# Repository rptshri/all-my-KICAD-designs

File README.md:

View this project on [CADLAB.io](https://cadlab.io/project/2196). 

# all-my-KICAD-designs

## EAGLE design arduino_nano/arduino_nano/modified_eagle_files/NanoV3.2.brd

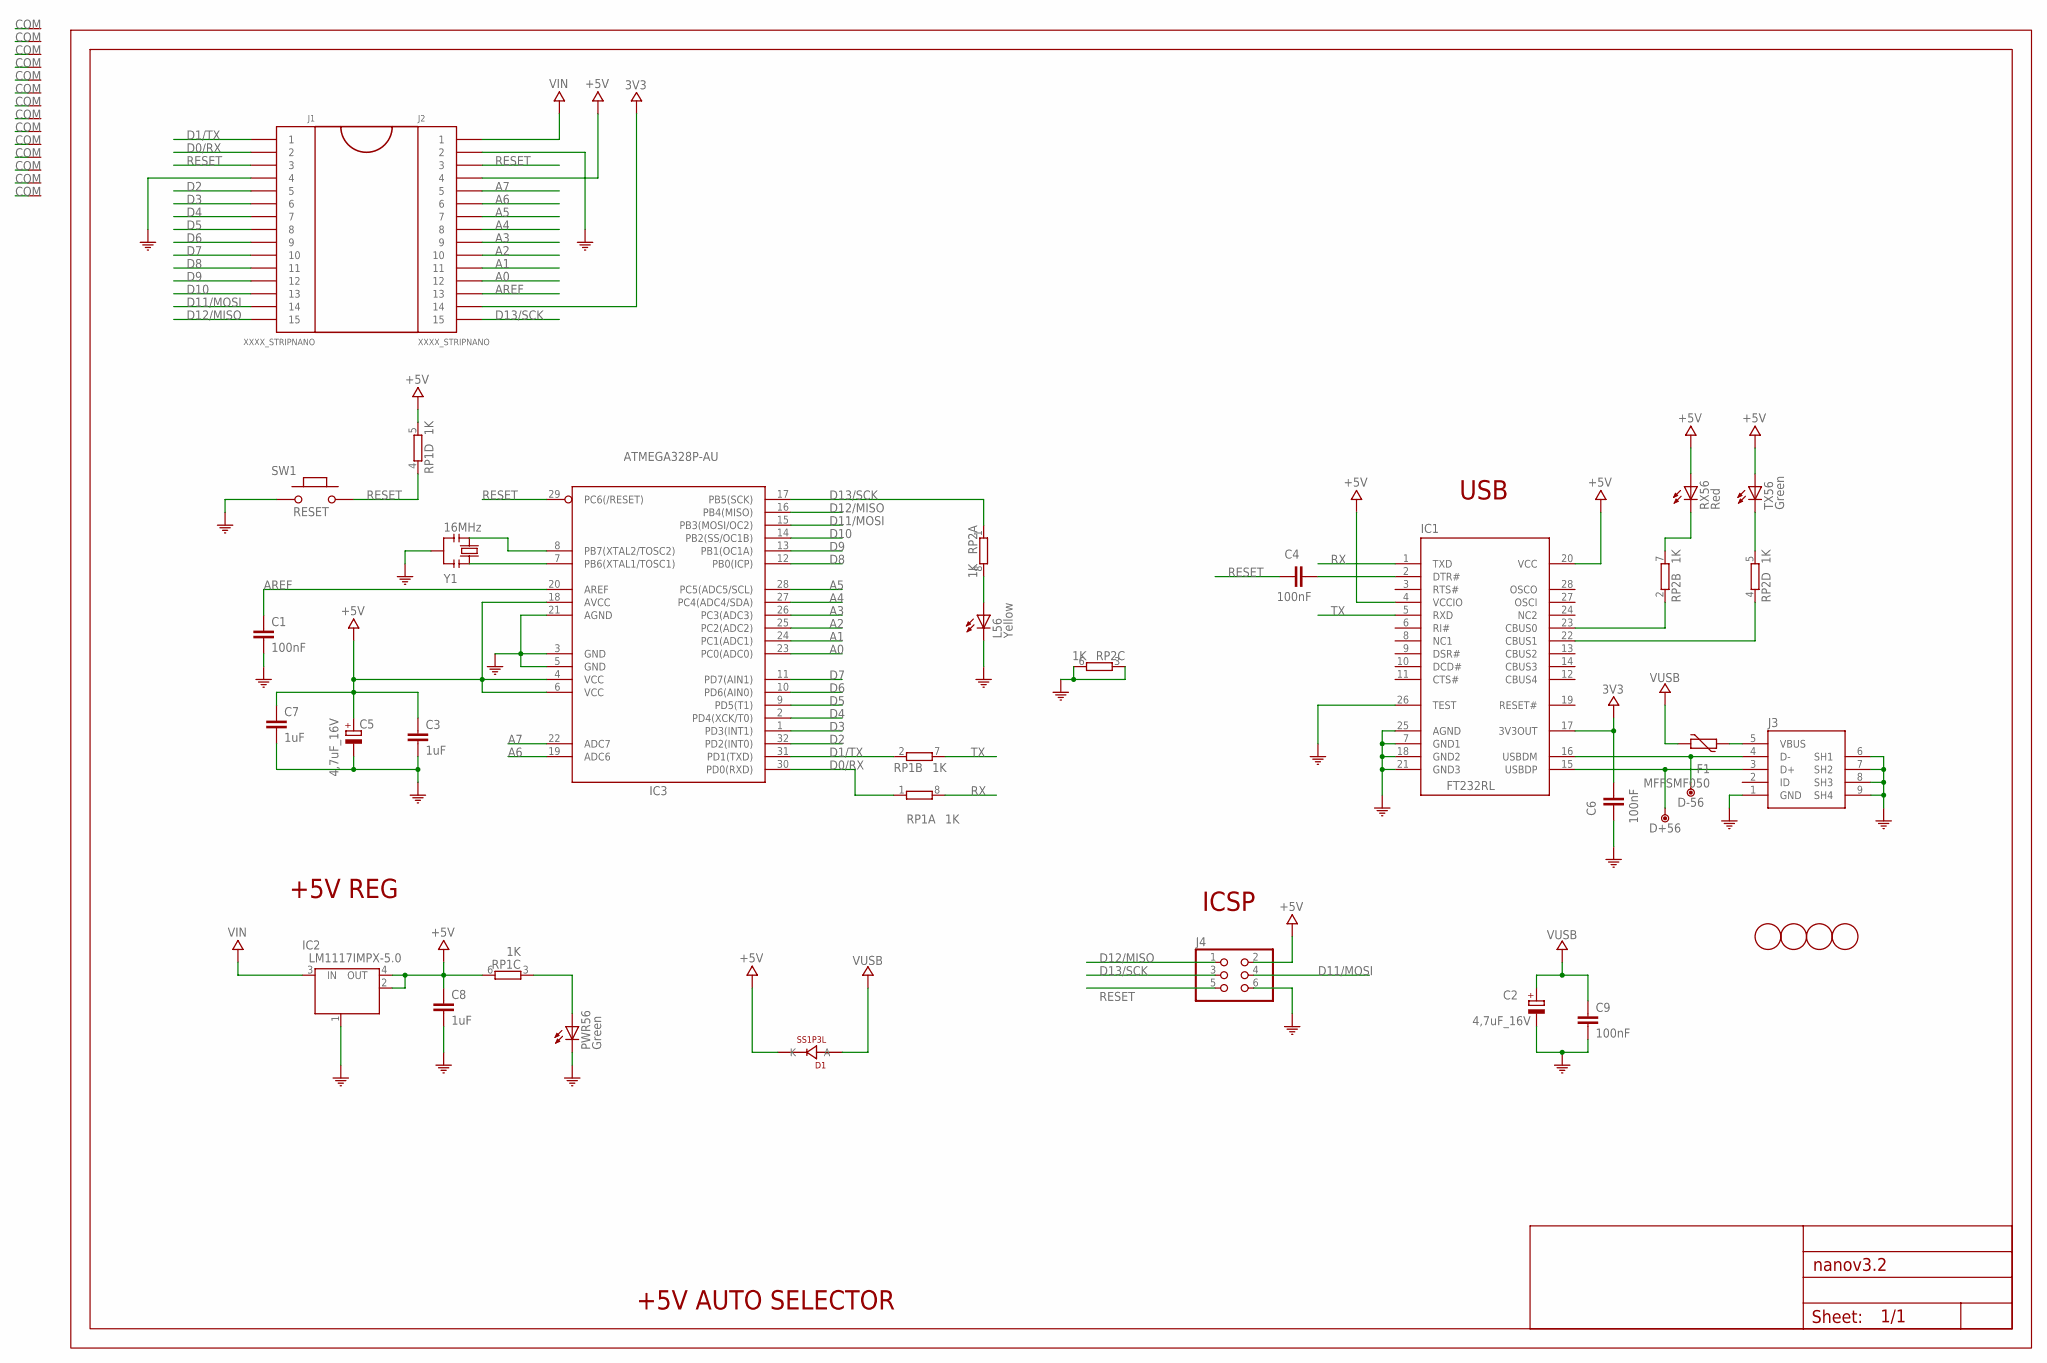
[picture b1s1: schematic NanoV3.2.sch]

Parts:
C1, C4, C6, C9: 100nF; C0603-ROUND
C2, C5: 4,7uF_16V; TAN-A
C3, C7, C8: 1uF; C0603-ROUND
D1: SS1P3L; DO220AAL
D+56: DNP; TP-1.00MM
D-56: DNP; TP-1.00MM
F1: MFFSMF050; 0603-1608X90N
FRAME1: DNP; FRAME
IC1: FT232RL; SSOP28
IC2: LM1117IMPX-5.0; LINEAR_SOT223
IC3: ATMEGA328P-AU; TQFP32-08
J1, J2: XXXX_STRIPNANO; HEAD15-NOSS
J3: 0219_14850; USB-MINI-B_2
J4: 0114_PH254-203DF118A00V; 2X03
L56: Yellow; CHIPLED_0805
PWR56: Green; CHIPLED_0805
RP1, RP2: 1K; CAY16
RX56: Red; CHIPLED_0805
SW1: RESET; SMD_157SW
TX56: Green; CHIPLED_0805
U$4, U$5, U$53, U$54: DNP; FD-1-1.5
VP_0, VP_1, VP_2, VP_3, VP_4, VP_5, VP_6, VP_7, VP_8, VP_9, VP_10, VP_11, VP_12, VP_13: VPDEV0; VPAC0
Y1: 16MHz; RESONATOR

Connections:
3V3: C6.2, IC1.17 (3V3OUT), J2.14
+5V: C3.1, C5.1 (+), C7.1, C8.1, D1.P$1 (K), IC1.4 (VCCIO), IC1.20 (VCC), IC2.2 (OUT), IC2.4 (OUT), IC3.4 (VCC), IC3.6 (VCC), IC3.18 (AVCC), J2.4, J4.2, RP1.5 (2), RP1.6 (2), RX56.A, TX56.A
A0: IC3.23 (PC0(ADC0)), J2.12
A1: IC3.24 (PC1(ADC1)), J2.11
A2: IC3.25 (PC2(ADC2)), J2.10
A3: IC3.26 (PC3(ADC3)), J2.9
A4: IC3.27 (PC4(ADC4/SDA)), J2.8
A5: IC3.28 (PC5(ADC5/SCL)), J2.7
A6: IC3.19 (ADC6), J2.6
A7: IC3.22 (ADC7), J2.5
AREF: C1.1, IC3.20 (AREF), J2.13
COM: C1.2, C2.2 (-), C3.2, C5.2 (-), C6.1, C7.2, C8.2, C9.2, IC1.7 (GND1), IC1.18 (GND2), IC1.21 (GND3), IC1.25 (AGND), IC1.26 (TEST), IC2.1 (GND/ADJ), IC3.3 (GND), IC3.5 (GND), IC3.21 (AGND), J1.4, J2.2, J3.1 (GND), J3.6 (SH1), J3.7 (SH2), J3.8 (SH3), J3.9 (SH4), J4.6, L56.C, PWR56.C, RP2.3 (1), RP2.6 (2), SW1.1, VP_0.VP, VP_1.VP, VP_2.VP, VP_3.VP, VP_4.VP, VP_5.VP, VP_6.VP, VP_7.VP, VP_8.VP, VP_9.VP, VP_10.VP, VP_11.VP, VP_12.VP, VP_13.VP, Y1.2
D0/RX: IC3.30 (PD0(RXD)), J1.2, RP1.1
D1/TX: IC3.31 (PD1(TXD)), J1.1, RP1.2 (1)
D2: IC3.32 (PD2(INT0)), J1.5
D3: IC3.1 (PD3(INT1)), J1.6
D4: IC3.2 (PD4(XCK/T0)), J1.7
D5: IC3.9 (PD5(T1)), J1.8
D6: IC3.10 (PD6(AIN0)), J1.9
D7: IC3.11 (PD7(AIN1)), J1.10
D8: IC3.12 (PB0(ICP)), J1.11
D9: IC3.13 (PB1(OC1A)), J1.12
D10: IC3.14 (PB2(SS/OC1B)), J1.13
D11/MOSI: IC3.15 (PB3(MOSI/OC2)), J1.14, J4.4
D12/MISO: IC3.16 (PB4(MISO)), J1.15, J4.1
D13/SCK: IC3.17 (PB5(SCK)), J2.15, J4.3, RP2.1
unnamed: IC3.8 (PB7(XTAL2/TOSC2)), Y1.3
unnamed: IC3.7 (PB6(XTAL1/TOSC1)), Y1.1
unnamed: PWR56.A, RP1.3 (1)
unnamed: C4.2, IC1.2 (DTR#)
unnamed: D+56.X, IC1.15 (USBDP), J3.3 (D+)
unnamed: D-56.X, IC1.16 (USBDM), J3.4 (D-)
unnamed: L56.A, RP2.8 (2)
unnamed: IC1.23 (CBUS0), RP2.2 (1)
unnamed: IC1.22 (CBUS1), RP2.4 (1)
unnamed: RP2.5 (2), TX56.C
unnamed: F1.2, J3.5 (VBUS)
unnamed: RP2.7 (2), RX56.C
RESET: C4.1, IC3.29 (PC6(/RESET)), J1.3, J2.3, J4.5, RP1.4 (1), SW1.2
RX: IC1.1 (TXD), RP1.8 (2)
TX: IC1.5 (RXD), RP1.7 (2)
VIN: IC2.3 (IN), J2.1
VUSB: C2.1 (+), C9.1, D1.P$2 (A), F1.1

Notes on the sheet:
+5V REG
ICSP
USB
+5V AUTO SELECTOR

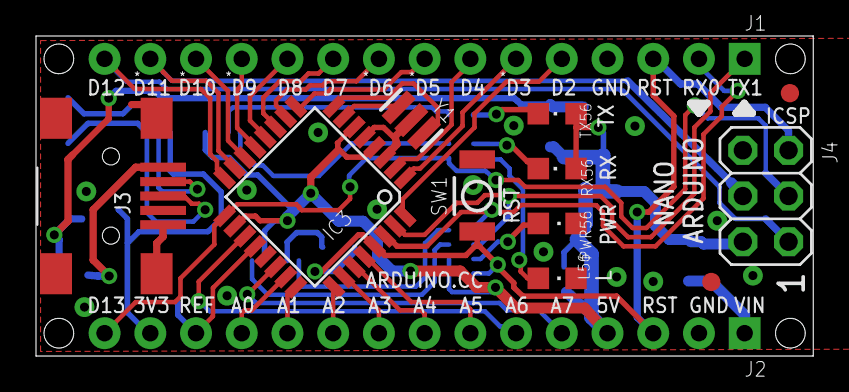
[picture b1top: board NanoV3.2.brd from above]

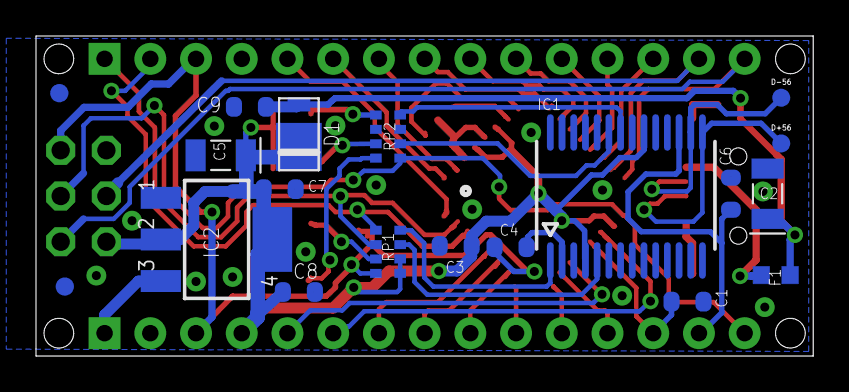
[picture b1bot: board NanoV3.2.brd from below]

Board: 2 copper layers, 43.2 x 17.8 mm, 47 parts (17 on the bottom side), 43 nets.

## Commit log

2019-03-20 added files
2019-03-28 nightly_l298n
2019-03-28 updated doc
2019-03-29 l298_driver completed
2019-04-06 arduino board files update
2019-04-11 upadte project files
2019-06-27 UPADATE
2019-08-17 library update
2019-09-12 update logo
2019-10-12 Backlink to CADLAB.io has been added.
2019-12-27 Soic8+DIP8_hybrid
2020-05-25 [ImgBot] Optimize images
    *Total -- 3,964.41kb -> 2,680.25kb (32.39%)
    /l298_dRIVER/l298_dRIVER-Edge.Cuts.svg -- 1.02kb -> 0.52kb (49.14%)
    /l298_dRIVER/l298_dRIVER-F.Cu.svg -- 50.30kb -> 26.43kb (47.44%)
    /arduino_nano/USB_TINY/USB_TINY-F.Cu.svg -- 392.74kb -> 248.95kb (36.61%)
    /controller_board/_autosave-controller_board-F.Cu.svg -- 495.48kb -> 319.44kb (35.53%)
    /controller_board/controller_board-F.Cu.svg -- 185.88kb -> 124.07kb (33.25%)

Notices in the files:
parts and their libraries:
Arduino-utility: Copyright (c) 2016-2017 Arduino LLC.  All right reserved.
